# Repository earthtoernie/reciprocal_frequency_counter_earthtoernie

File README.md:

# Reciprocal frequency counter for Raspberry pi pico

Shield: [![CC BY-SA 4.0][cc-by-sa-shield]][cc-by-sa]

This work is licensed under a
[Creative Commons Attribution-ShareAlike 4.0 International License][cc-by-sa].

[![CC BY-SA 4.0][cc-by-sa-image]][cc-by-sa]

[cc-by-sa]: http://creativecommons.org/licenses/by-sa/4.0/
[cc-by-sa-image]: https://licensebuttons.net/l/by-sa/4.0/88x31.png
[cc-by-sa-shield]: https://img.shields.io/badge/License-CC%20BY--SA%204.0-lightgrey.svg

## Citation
[Rrciprocal frequency counter](https://forums.raspberrypi.com/viewtopic.php?t=306250)
 The guts of the "pio" code was copied from this thread, and slightly modified and translated from "micropython"
 Display stuff, and PCB is my own.

## Main project
[The counter](pico_display_oled/main.cpp)

## Circuit board
[kicad board](kicad_pico_counter_new)

## Background
- Wanted to make a speed sensor to detect gear teeth for some application. Did not need to use a "Reciprocal frequency counter" and / or such
a complicated "pio" setup, but decided to go down this route anyway.

- Picked a part from "Allegro microsystems" to do the sensing. There was no "Development board" available, but this should be just as good :)

- "ATS19480: Large Air Gap, GMR Speed Sensor IC for Gear Tooth Sensing" is the part. Should be available on Digikey or Mouser.

## Features
- Circuit board has a "driver" to read from a 2 terminal device. Window comparator added to translate discrete states of current, to 3.3 IO voltage.
This is for compatibility with GPIO on the pico board.

- Have had success using the sensor to read from the position 

- Button to change the window size

- Reset button (the pico board should have had this from the get go)

- Button to switch between sensor input, and input from 50ohm source (function generator)

## Brag
Was able to conveniently run from the 5V usb power source, with no additional boost converter.

## Awesome script to install sdk on Ubuntu 23.04
[install script](NOTES/install_raspberry_pico.sh) 

# Notes
Some other junk is included in this project (interfacing with other sensors), feel free to ignore. Also other "Scratch" projects included

sudo minicom -D /dev/ttyACM0 -b 115200  

Also examples from [pimoroni C examples](https://github.com/pimoroni/pimoroni-pico/tree/main/examples)  
how to setup IDE [Pico + cLion](https://forums.raspberrypi.com/viewtopic.php?t=310446)

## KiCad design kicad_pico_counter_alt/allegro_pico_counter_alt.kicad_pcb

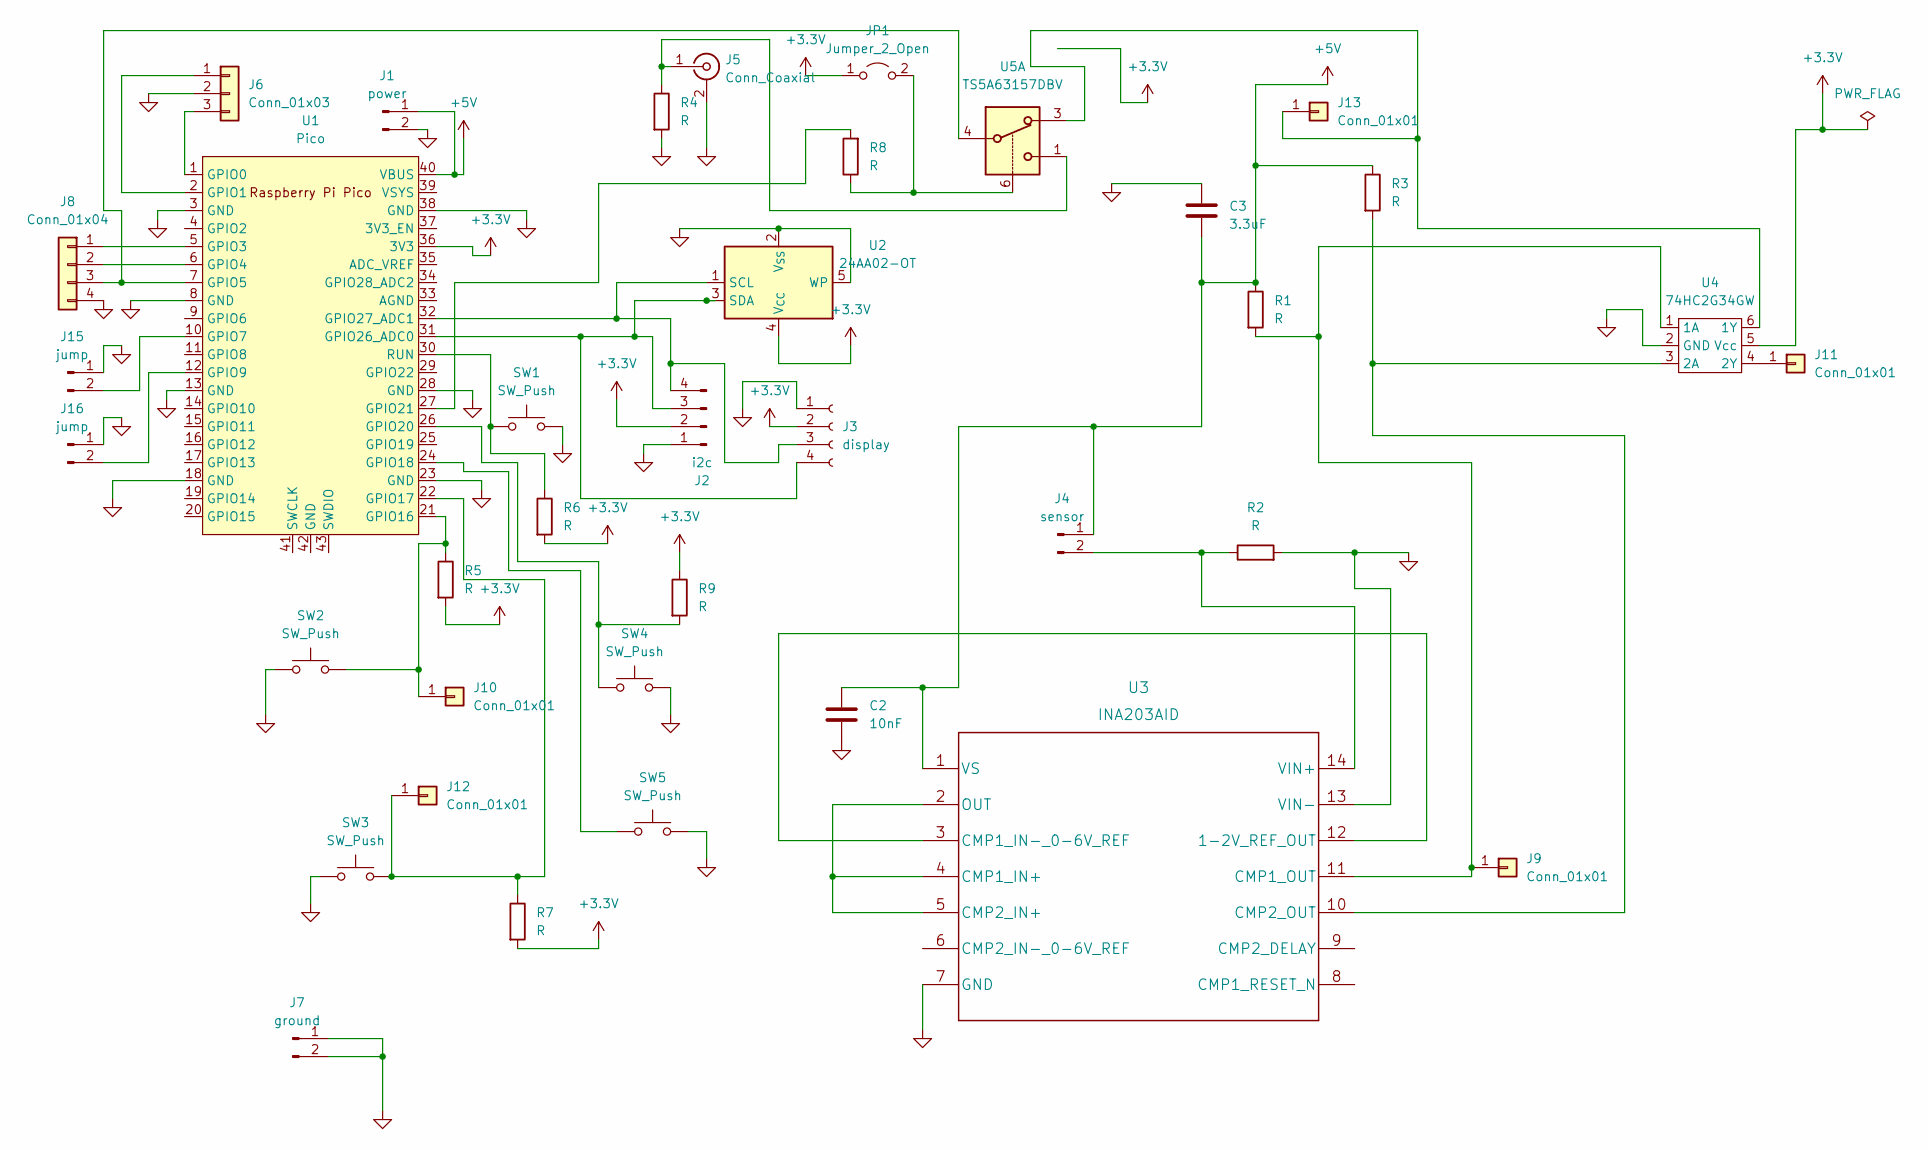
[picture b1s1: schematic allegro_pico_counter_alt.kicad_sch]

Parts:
C2: 10nF; C_0805_2012Metric
C3: 3.3uF; C_0805_2012Metric
J1: power; PinHeader_1x02_P2.54mm_Vertical
J2: i2c; JST_SH_SM04B-SRSS-TB_1x04-1MP_P1.00mm_Horizontal
J3: display; PinHeader_1x04_P2.54mm_Vertical
J4: sensor; PinHeader_1x02_P2.54mm_Vertical
J5: Conn_Coaxial; SMB_Jack_Vertical
J6: Conn_01x03; JST_SH_SM03B-SRSS-TB_1x03-1MP_P1.00mm_Horizontal
J7: ground; PinHeader_1x02_P2.54mm_Vertical
J8: Conn_01x04; PinHeader_1x04_P2.54mm_Vertical
J9, J10, J11, J12, J13: Conn_01x01; PinHeader_1x01_P2.54mm_Vertical
J15, J16: jump; PinHeader_1x02_P2.54mm_Vertical
JP1: Jumper_2_Open; PinHeader_1x02_P2.54mm_Vertical
R1, R2, R3, R4, R5, R6, R7, R8, R9: R; R_0805_2012Metric
SW1, SW2, SW3, SW4, SW5: SW_Push; SW_SPST_CK_RS282G05A3
U1: Pico; RPi_Pico_SMD_TH
U2: 24AA02-OT; SOT-23-5
U3: INA203AID
U4: 74HC2G34GW; SOT-363_SC-70-6_Handsoldering
U5: TS5A63157DBV; SOT-23-6

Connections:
+3.3V: J2.2, J3.2, JP1.1 (A), R5.2, R6.2, R7.2, R9.1, U1.36 (3V3), U2.4 (V_{CC}), U4.5 (Vcc); also elsewhere on the board
+5V: C2.1, C3.2, J1.1, J4.1, R1.1, R3.1, U1.40 (VBUS), U3.1 (VS)
GND: C2.2, C3.1, J1.2, J2.1, J3.1, J5.2 (Ext), J6.2, J7.1, J7.2, J8.4, J15.1, J16.1, R2.2, R4.2, SW1.2, SW2.1, SW3.1, SW4.2, SW5.2, U1.3 (GND), U1.8 (GND), U1.13 (GND), U1.18 (GND), U1.23 (GND), U1.28 (GND), U1.38 (GND), U2.2 (V_{SS}), U2.5 (WP), U3.7 (GND), U3.13 (VIN-), U4.2 (GND)
unnamed 3: J2.3, J3.4, U1.31 (GPIO26_ADC0), U2.3 (SDA); also elsewhere on the board
unnamed 4: J2.4, J3.3, U1.32 (GPIO27_ADC1), U2.1 (SCL); also elsewhere on the board
unnamed: J4.2, R2.1, U3.14 (VIN+)
unnamed: J5.1 (In), R4.1, U5.1
unnamed: J6.1, U1.2 (GPIO1)
unnamed: J6.3, U1.1 (GPIO0)
unnamed: J8.1, U1.5 (GPIO3)
unnamed: J8.2, U1.6 (GPIO4)
unnamed: J8.3, U1.7 (GPIO5), U5.4
unnamed: J9.1, R1.2, U3.11 (CMP1_OUT), U4.1 (1A)
unnamed: J10.1, R5.1, SW2.2, U1.21 (GPIO16)
unnamed: J11.1, U4.4 (2Y)
unnamed: J12.1, R7.1, SW3.2, U1.22 (GPIO17)
unnamed: J13.1, U4.6 (1Y), U5.3
unnamed: J15.2, U1.10 (GPIO7)
unnamed: J16.2, U1.12 (GPIO9)
unnamed: JP1.2 (B), R8.1, U5.6
unnamed: SW5.1, U1.24 (GPIO18)
unnamed: R9.2, SW4.1, U1.26 (GPIO20)
unnamed: R8.2, U1.27 (GPIO21)
unnamed: R6.1, SW1.1, U1.30 (RUN)
unnamed: U3.3 (CMP1_IN-_0-6V_REF), U3.12 (1-2V_REF_OUT)
unnamed: U3.2 (OUT), U3.4 (CMP1_IN+), U3.5 (CMP2_IN+)
unnamed: R3.2, U3.10 (CMP2_OUT), U4.3 (2A)

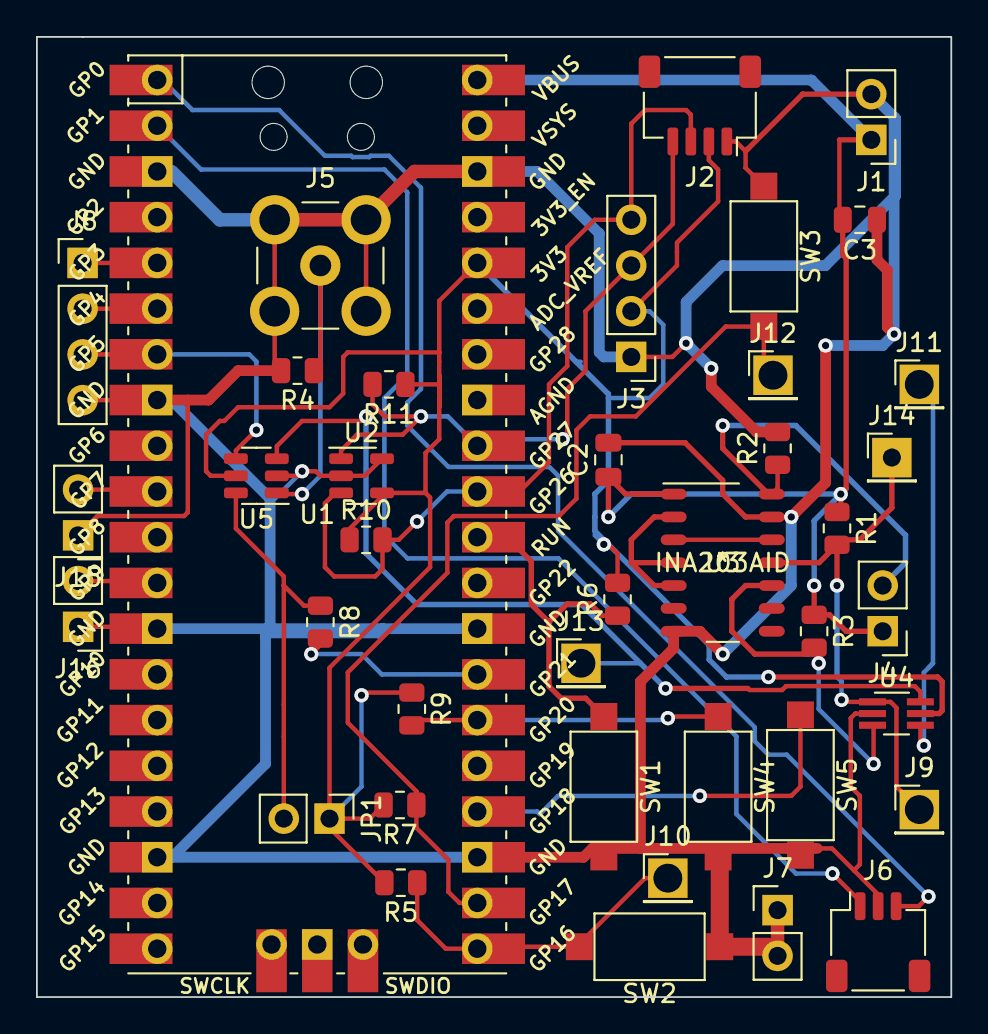
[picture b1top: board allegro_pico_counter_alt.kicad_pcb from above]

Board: 2 copper layers, 50.8 x 53.3 mm, 40 parts (0 on the bottom side), 27 nets.

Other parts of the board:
J14: Conn_01x01; PinHeader_1x01_P2.54mm_Vertical
R10, R11: R; R_0805_2012Metric

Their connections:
+3.3V: R10.1, R11.1; also elsewhere on the board
unnamed 3: R10.2; also elsewhere on the board
unnamed 4: R11.2; also elsewhere on the board

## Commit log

2021-12-12 add pimoroni libraries and drivers
2021-12-12 remove github workflow scope
2021-12-12 get the pico-display working
2021-12-18 fix blink hello world, and start sht40 empty project
2021-12-19 sht40 prints temp and rh
2021-12-30 small changes
2022-01-01 gst some display stuff to work
2022-01-10 make pwm demo set two pins, update counter stuff
2022-01-24 work on graphics
2022-02-06 get to pio_counter_milestone_0
2022-02-07 try to get pio_counter_milestone_1 to work
2022-02-10 prints interesting pattern with some letters across pico display
2022-02-12 get temp humidity sht40 working with display
2022-02-13 add new project to test pio interrupts
2022-02-13 make the program blink
2022-02-13 sideset works somewhat
2022-02-13 interrupt program works
2022-02-13 pio_counter_milestone_1.py matches waveform with program
2022-02-13 read with pio_sm_get to get buffer
2022-02-13 almost exact same waveforms for final program
2022-02-13 clean up printing
2022-02-20 almost in sync with just the gate
2022-02-20 continue working
2022-02-20 interesting weird stuff
2022-02-20 whoa interesting pattern
2022-02-20 kinda interesting
2022-02-21 fix init of sm 2
2022-02-21 all works, off by a tiny bit
2022-02-21 super small change
2022-02-25 stub out pico oled program, (annd add empty lib) but has undefined reference to blinkForever()
2022-03-06 can get some snow on oled display
2022-03-06 counter prints to oled
2022-03-06 clean up some
2022-03-12 change gate time to 20ms
2022-03-13 add different gate times
2022-07-09 tiny changes
2023-04-20 add working vscode config that uses ninja to build
2023-04-21 add notes and install script for rpi sdk
2023-05-07 update license, add pictures, update readme
2023-05-07 moreve a bunch of stuff
2023-05-07 fix typo
2023-05-07 clean up
2023-05-07 remove some more junk
2023-05-08 fix cmake
2023-05-13 add switch stuff
2023-05-14 update kicad and gitignore
2023-05-14 work on switch logic for inputs
2023-05-14 update callback code , and pcb layout
2023-05-14 update irq code
2023-05-14 update doc
2023-05-15 try some craszy stuff
2023-05-15 still working on debounce
2023-05-16 update button function
2023-05-30 add new pcb and schematic version, and change a pin in the code
2023-06-11 Update part_notes.txt
    add parts list
2023-10-26 update script
2023-11-05 start empty squaregen project
2023-11-13 update squaregen boilerplate

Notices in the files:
parts and their libraries:
Copyright 2021 Accelerated Designs. All rights reserved.
